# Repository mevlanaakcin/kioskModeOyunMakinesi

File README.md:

# kioskModeOyunMakinesi
Kiosk Modda çalışan eğlence amaçlı oyun makinesi<br>
<h3>PCB Tasarımı</h3><br>
Elektronik devre şeması ve PCB board tasarımı Eagle de tasarlandı.<br>

<h3>Yazılım</h3><br>
Yalım bölümü Atmega328-P işlemci kullanıldığından Raspberrypi ile tasarlanan kart arasında Serial haberleşme yapılmıştır. Kart üzerinde bulunan servo motorlar ile ödül dağıtım kanallarını kontrol edilmektedir. Görsel amaçlı kullanılan neopiksellerin yazılımsal kontrolleride yapılmıştır.

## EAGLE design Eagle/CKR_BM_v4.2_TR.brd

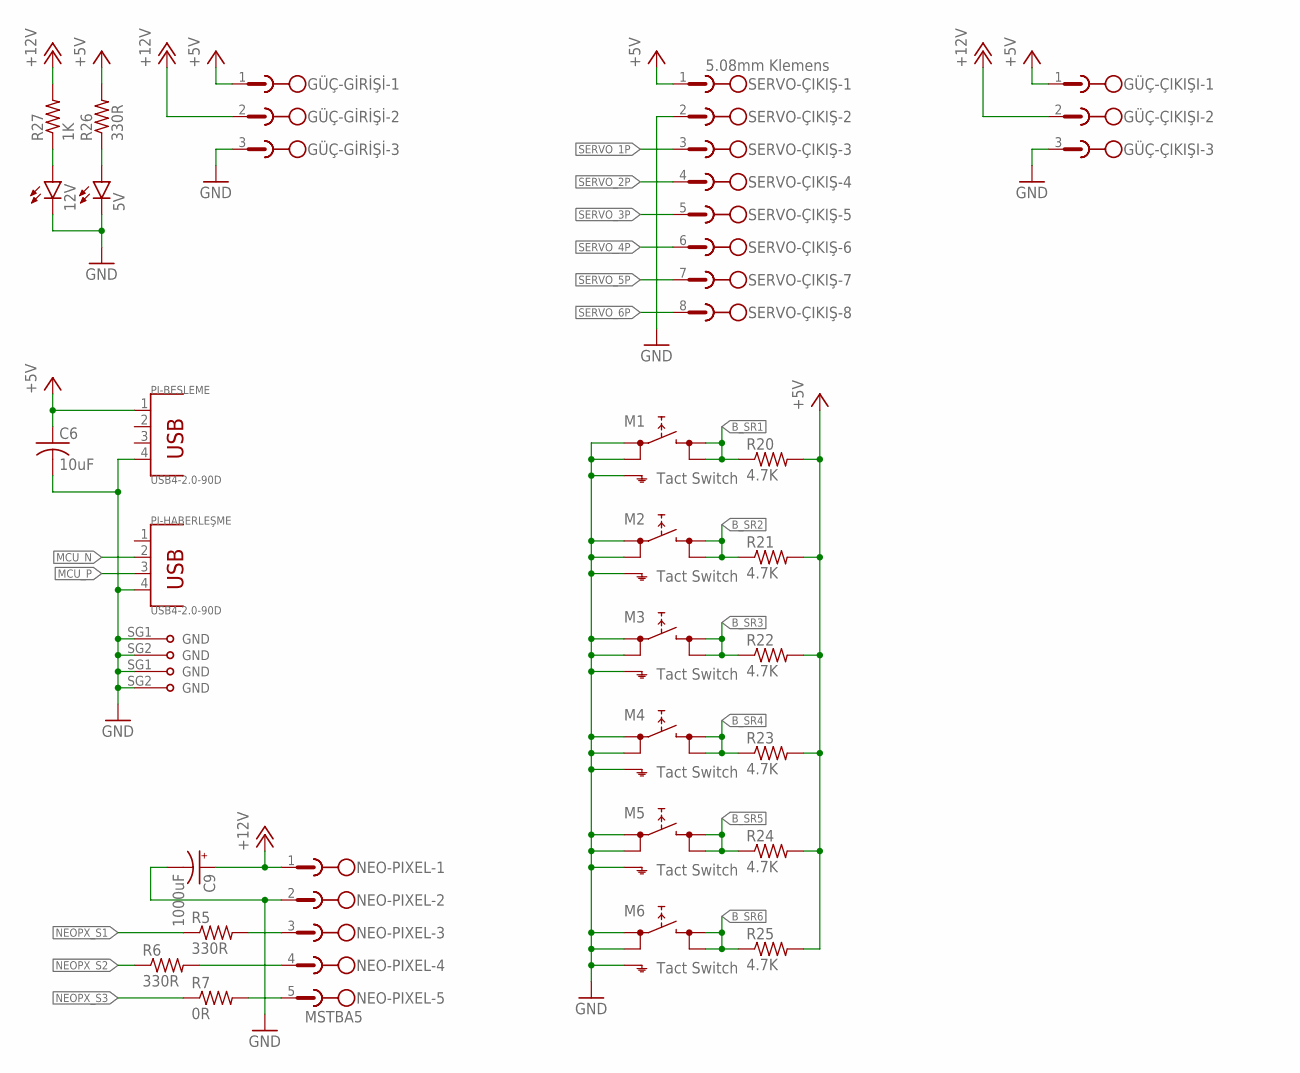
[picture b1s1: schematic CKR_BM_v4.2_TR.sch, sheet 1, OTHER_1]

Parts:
5V, 12V: LEDCHIP-LED0805; CHIP-LED0805
C6: 10uF; C0805
C9: 1000uF; 140CLH-1010
GÜÇ-GİRİŞİ: 5.08mm Klemens; MSTBA3
GÜÇ-ÇIKIŞI: 5.08mm Klemens; MSTBA3
M1, M2, M3, M4, M5, M6: Tact Switch; SKHMPXE010
NEO-PIXEL: MSTBA5
PI-BESLEME: USB4-2.0-90D; USB4+2P-2.0-90D
PI-HABERLEŞME: USB4-2.0-90D; USB4+2P-2.0-90D
R5, R6, R26: 330R; R0805
R7: 0R; R0805
R20, R21, R22, R23, R24, R25: 4.7K; R0805
R27: 1K; R0805
SERVO-ÇIKIŞ: 5.08mm Klemens; MSTBA8

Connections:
+5V: C6.1, GÜÇ-GİRİŞİ.1, GÜÇ-ÇIKIŞI.1, PI-BESLEME.1, R20.2, R21.2, R22.2, R23.2, R24.2, R25.2, R26.2, SERVO-ÇIKIŞ.1; also elsewhere on the board
+12V: C9.+, GÜÇ-GİRİŞİ.2, GÜÇ-ÇIKIŞI.2, NEO-PIXEL.1, R27.2; also elsewhere on the board
B_SR1: M1.3 (2.1), M1.4 (2.2), R20.1; also elsewhere on the board
B_SR2: M2.3 (2.1), M2.4 (2.2), R21.1; also elsewhere on the board
B_SR3: M3.3 (2.1), M3.4 (2.2), R22.1; also elsewhere on the board
B_SR4: M4.3 (2.1), M4.4 (2.2), R23.1; also elsewhere on the board
B_SR5: M5.3 (2.1), M5.4 (2.2), R24.1; also elsewhere on the board
B_SR6: M6.3 (2.1), M6.4 (2.2), R25.1; also elsewhere on the board
GND: 5V.C, 12V.C, C6.2, C9.-, GÜÇ-GİRİŞİ.3, GÜÇ-ÇIKIŞI.3, M1.1 (1.1), M1.2 (1.2), M1.5 (SH), M2.1 (1.1), M2.2 (1.2), M2.5 (SH), M3.1 (1.1), M3.2 (1.2), M3.5 (SH), M4.1 (1.1), M4.2 (1.2), M4.5 (SH), M5.1 (1.1), M5.2 (1.2), M5.5 (SH), M6.1 (1.1), M6.2 (1.2), M6.5 (SH), NEO-PIXEL.2, PI-BESLEME.4, PI-BESLEME.SG1 (GND), PI-BESLEME.SG2 (GND), PI-HABERLEŞME.4, PI-HABERLEŞME.SG1 (GND), PI-HABERLEŞME.SG2 (GND), SERVO-ÇIKIŞ.2; also elsewhere on the board
MCU_N: PI-HABERLEŞME.2; also elsewhere on the board
MCU_P: PI-HABERLEŞME.3; also elsewhere on the board
unnamed: NEO-PIXEL.3, R5.2
unnamed: NEO-PIXEL.4, R6.2
unnamed: NEO-PIXEL.5, R7.2
unnamed: 5V.A, R26.1
unnamed: 12V.A, R27.1
NEOPX_S1: R5.1; also elsewhere on the board
NEOPX_S2: R6.1; also elsewhere on the board
NEOPX_S3: R7.1; also elsewhere on the board
SERVO_1P: SERVO-ÇIKIŞ.3; also elsewhere on the board
SERVO_2P: SERVO-ÇIKIŞ.4; also elsewhere on the board
SERVO_3P: SERVO-ÇIKIŞ.5; also elsewhere on the board
SERVO_4P: SERVO-ÇIKIŞ.6; also elsewhere on the board
SERVO_5P: SERVO-ÇIKIŞ.7; also elsewhere on the board
SERVO_6P: SERVO-ÇIKIŞ.8; also elsewhere on the board

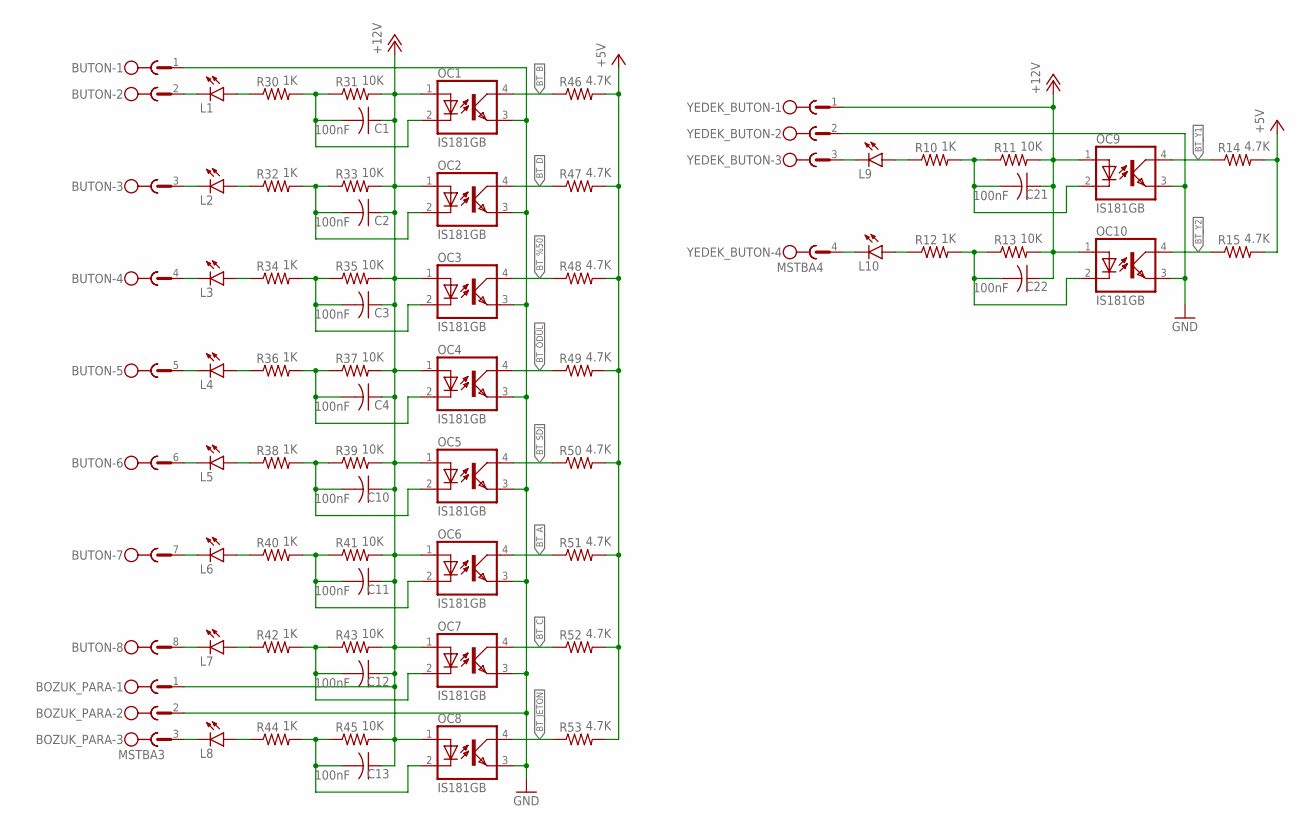
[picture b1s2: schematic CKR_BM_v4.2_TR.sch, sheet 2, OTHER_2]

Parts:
BOZUK_PARA: MSTBA3
BUTON: MSTBA8
C1, C2, C3, C4, C10, C11, C12, C13, C21, C22: 100nF; C0805
L1, L2, L3, L4, L5, L6, L7, L8, L9, L10: LEDCHIP-LED0805; CHIP-LED0805
OC1, OC2, OC3, OC4, OC5, OC6, OC7, OC8, OC9, OC10: IS181GB; SO-4
R10, R12, R30, R32, R34, R36, R38, R40, R42, R44: 1K; R0805
R11, R13, R31, R33, R35, R37, R39, R41, R43, R45: 10K; R0805
R14, R15, R46, R47, R48, R49, R50, R51, R52, R53: 4.7K; R0805
YEDEK_BUTON: MSTBA4

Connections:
+5V: R14.2, R15.2, R46.2, R47.2, R48.2, R49.2, R50.2, R51.2, R52.2, R53.2; also elsewhere on the board
+12V: BOZUK_PARA.1, C1.1, C2.1, C3.1, C4.1, C10.1, C11.1, C12.1, C13.1, C21.1, C22.1, OC1.1 (A), OC2.1 (A), OC3.1 (A), OC4.1 (A), OC5.1 (A), OC6.1 (A), OC7.1 (A), OC8.1 (A), OC9.1 (A), OC10.1 (A), R11.2, R13.2, R31.2, R33.2, R35.2, R37.2, R39.2, R41.2, R43.2, R45.2, YEDEK_BUTON.1; also elsewhere on the board
BT_%50: OC3.4 (COL), R48.1; also elsewhere on the board
BT_A: OC6.4 (COL), R51.1; also elsewhere on the board
BT_B: OC1.4 (COL), R46.1; also elsewhere on the board
BT_C: OC7.4 (COL), R52.1; also elsewhere on the board
BT_D: OC2.4 (COL), R47.1; also elsewhere on the board
BT_JETON: OC8.4 (COL), R53.1; also elsewhere on the board
BT_SDJ: OC5.4 (COL), R50.1; also elsewhere on the board
BT_Y1: OC9.4 (COL), R14.1; also elsewhere on the board
BT_Y2: OC10.4 (COL), R15.1; also elsewhere on the board
BT_ÖDÜL: OC4.4 (COL), R49.1; also elsewhere on the board
GND: BOZUK_PARA.2, BUTON.1, OC1.3 (EMIT), OC2.3 (EMIT), OC3.3 (EMIT), OC4.3 (EMIT), OC5.3 (EMIT), OC6.3 (EMIT), OC7.3 (EMIT), OC8.3 (EMIT), OC9.3 (EMIT), OC10.3 (EMIT), YEDEK_BUTON.2; also elsewhere on the board
unnamed: L1.A, R30.1
unnamed: C1.2, OC1.2 (C), R30.2, R31.1
unnamed: L9.A, R10.1
unnamed: BUTON.2, L1.C
unnamed: BOZUK_PARA.3, L8.C
unnamed: L2.A, R32.1
unnamed: C2.2, OC2.2 (C), R32.2, R33.1
unnamed: C21.2, OC9.2 (C), R10.2, R11.1
unnamed: BUTON.8, L7.C
unnamed: L3.A, R34.1
unnamed: C3.2, OC3.2 (C), R34.2, R35.1
unnamed: L9.C, YEDEK_BUTON.3
unnamed: BUTON.7, L6.C
unnamed: L4.A, R36.1
unnamed: C4.2, OC4.2 (C), R36.2, R37.1
unnamed: L10.A, R12.1
unnamed: BUTON.6, L5.C
unnamed: L5.A, R38.1
unnamed: C10.2, OC5.2 (C), R38.2, R39.1
unnamed: C22.2, OC10.2 (C), R12.2, R13.1
unnamed: BUTON.5, L4.C
unnamed: L6.A, R40.1
unnamed: C11.2, OC6.2 (C), R40.2, R41.1
unnamed: L10.C, YEDEK_BUTON.4
unnamed: BUTON.4, L3.C
unnamed: L7.A, R42.1
unnamed: C12.2, OC7.2 (C), R42.2, R43.1
unnamed: BUTON.3, L2.C
unnamed: L8.A, R44.1
unnamed: C13.2, OC8.2 (C), R44.2, R45.1

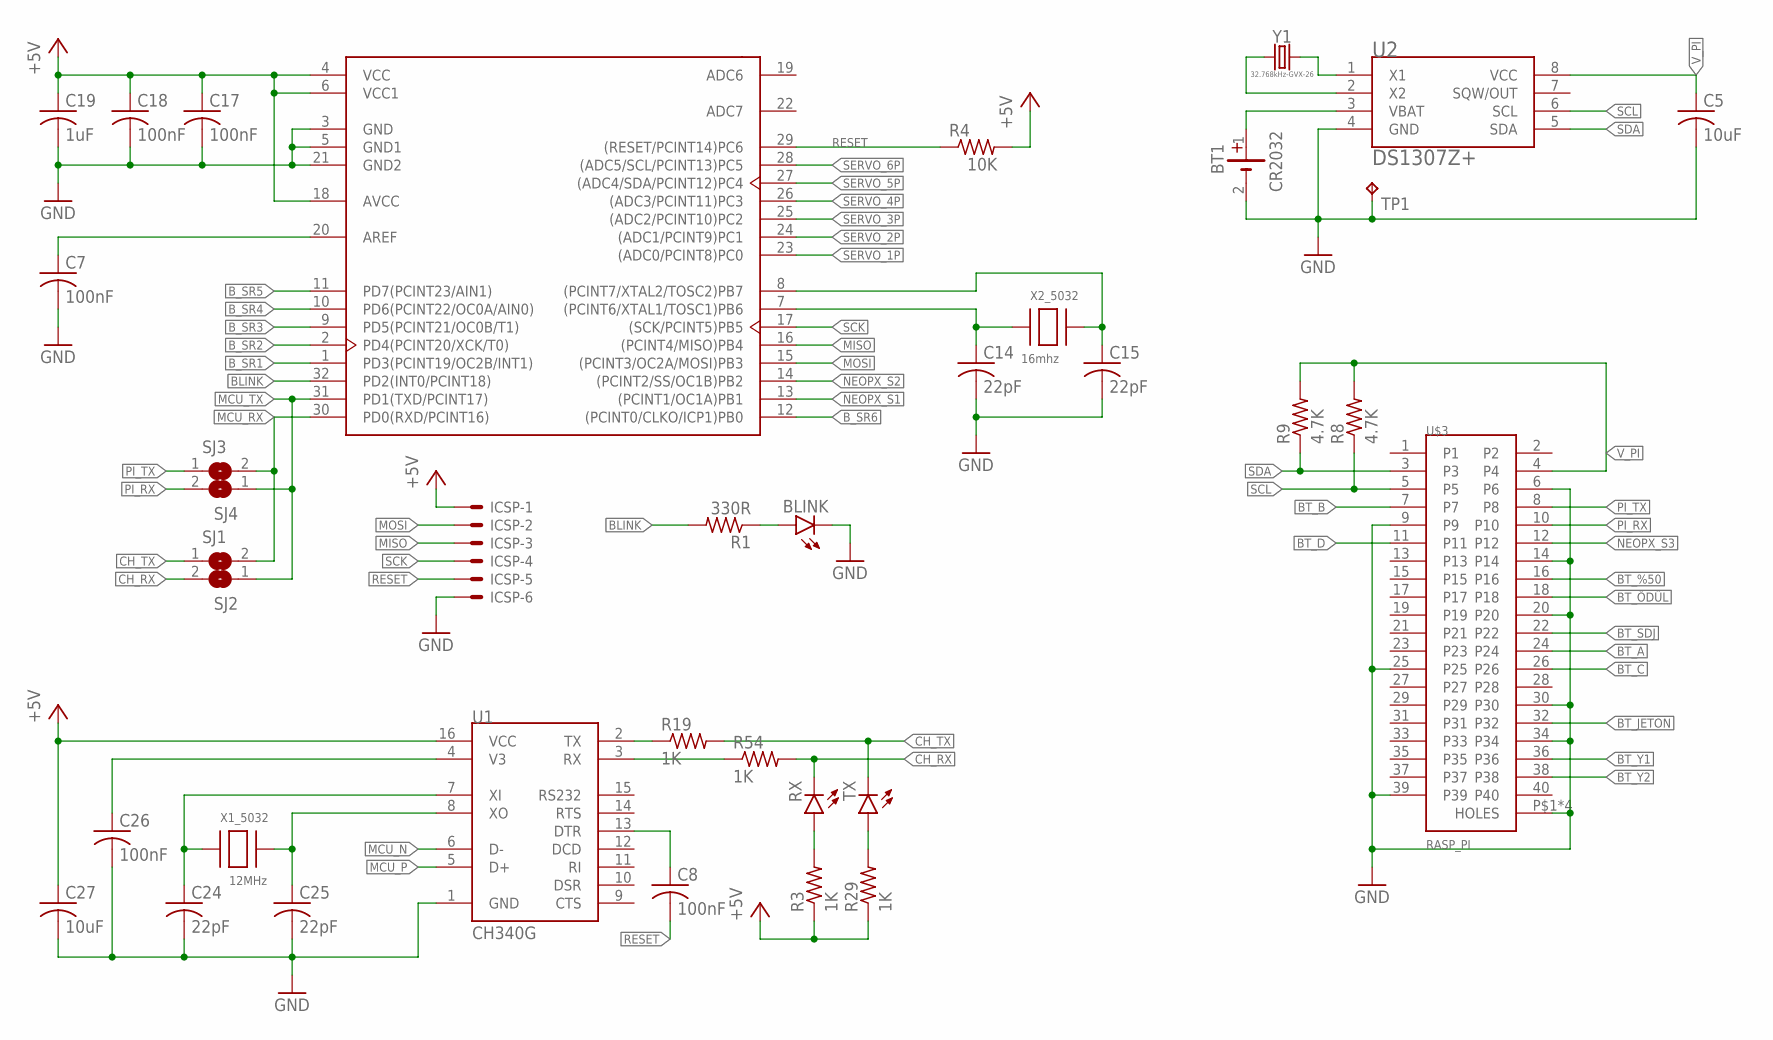
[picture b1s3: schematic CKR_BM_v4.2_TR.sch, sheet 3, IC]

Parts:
BLINK: LEDCHIP-LED0805; CHIP-LED0805
BT1: CR2032; 79528211
C5, C27: 10uF; C0805
C7, C8, C17, C18, C26: 100nF; C0805
C14, C15, C24, C25: 22pF; C0805
C19: 1uF; C0805
ICSP: C-GRID-06-70543; 70543-06
R1: 330R; R0805
R3, R19, R29, R54: 1K; R0805
R4: 10K; R0805
R8, R9: 4.7K; R0805
RX: LEDCHIP-LED0805; CHIP-LED0805
SJ1, SJ2, SJ3, SJ4: SJ
TP1: GND; TP15R
TX: LEDCHIP-LED0805; CHIP-LED0805
U1: CH340G; SOIC16
U2: DS1307Z+; SOIC-8N
U4: ATMEGA328P-AU; TQFP-32
U$3: RASP_PI
X1_5032: 12MHz; NX5032
X2_5032: 16mhz; NX5032
Y1: 32.768kHz-GVX-26; CRYSTAL-PTH-2X6-CYL

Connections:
+5V: C17.1, C18.1, C19.1, C27.1, ICSP.1, R3.1, R4.2, R29.1, U1.16 (VCC), U4.4 (VCC), U4.6 (VCC1), U4.18 (AVCC); also elsewhere on the board
BLINK: R1.2, U4.32 (PD2(INT0/PCINT18))
BT_%50: U$3.16; also elsewhere on the board
BT_A: U$3.24; also elsewhere on the board
BT_B: U$3.7; also elsewhere on the board
BT_C: U$3.26; also elsewhere on the board
BT_D: U$3.11; also elsewhere on the board
BT_JETON: U$3.32; also elsewhere on the board
BT_SDJ: U$3.22; also elsewhere on the board
BT_Y1: U$3.36; also elsewhere on the board
BT_Y2: U$3.38; also elsewhere on the board
BT_ÖDÜL: U$3.18; also elsewhere on the board
B_SR1: U4.1 (PD3(PCINT19/OC2B/INT1)); also elsewhere on the board
B_SR2: U4.2 (PD4(PCINT20/XCK/T0)); also elsewhere on the board
B_SR3: U4.9 (PD5(PCINT21/OC0B/T1)); also elsewhere on the board
B_SR4: U4.10 (PD6(PCINT22/OC0A/AIN0)); also elsewhere on the board
B_SR5: U4.11 (PD7(PCINT23/AIN1)); also elsewhere on the board
B_SR6: U4.12 ((PCINT0/CLKO/ICP1)PB0); also elsewhere on the board
CH_RX: R54.2, RX.C, SJ2.2
CH_TX: R19.2, SJ1.1, TX.C
GND: BLINK.C, BT1.2 (-), C5.2, C7.2, C14.2, C15.2, C17.2, C18.2, C19.2, C24.2, C25.2, C26.2, C27.2, ICSP.6, TP1.TP, U1.1 (GND), U2.4 (GND), U4.3 (GND), U4.5 (GND1), U4.21 (GND2), U$3.6, U$3.9, U$3.14, U$3.20, U$3.25, U$3.30, U$3.34, U$3.39, U$3.P$1 (HOLES), U$3.P$2 (HOLES), U$3.P$3 (HOLES), U$3.P$4 (HOLES); also elsewhere on the board
MCU_N: U1.6 (D-); also elsewhere on the board
MCU_P: U1.5 (D+); also elsewhere on the board
MCU_RX: SJ1.2, SJ3.2, U4.30 (PD0(RXD/PCINT16))
MCU_TX: SJ2.1, SJ4.1, U4.31 (PD1(TXD/PCINT17))
MISO: ICSP.3, U4.16 ((PCINT4/MISO)PB4)
MOSI: ICSP.2, U4.15 ((PCINT3/OC2A/MOSI)PB3)
unnamed: BT1.1 (+), U2.3 (VBAT)
unnamed: U2.2 (X2), Y1.1
unnamed: U2.1 (X1), Y1.2
unnamed: R3.2, RX.A
unnamed: R29.2, TX.A
unnamed: C14.1, U4.7 ((PCINT6/XTAL1/TOSC1)PB6), X2_5032.P$1
unnamed: C8.1, U1.13 (DTR)
unnamed: C26.1, U1.4 (V3)
unnamed: C24.1, U1.7 (XI), X1_5032.P$1
unnamed: C25.1, U1.8 (XO), X1_5032.P$2
unnamed: R19.1, U1.2 (TX)
unnamed: R54.1, U1.3 (RX)
unnamed: BLINK.A, R1.1
unnamed: C7.1, U4.20 (AREF)
unnamed: C15.1, U4.8 ((PCINT7/XTAL2/TOSC2)PB7), X2_5032.P$2
NEOPX_S1: U4.13 ((PCINT1/OC1A)PB1); also elsewhere on the board
NEOPX_S2: U4.14 ((PCINT2/SS/OC1B)PB2); also elsewhere on the board
NEOPX_S3: U$3.12; also elsewhere on the board
PI_RX: SJ4.2, U$3.10
PI_TX: SJ3.1, U$3.8
RESET: C8.2, ICSP.5, R4.1, U4.29 ((RESET/PCINT14)PC6)
SCK: ICSP.4, U4.17 ((SCK/PCINT5)PB5)
SCL: R8.1, U2.6 (SCL), U$3.5
SDA: R9.1, U2.5 (SDA), U$3.3
SERVO_1P: U4.23 ((ADC0/PCINT8)PC0); also elsewhere on the board
SERVO_2P: U4.24 ((ADC1/PCINT9)PC1); also elsewhere on the board
SERVO_3P: U4.25 ((ADC2/PCINT10)PC2); also elsewhere on the board
SERVO_4P: U4.26 ((ADC3/PCINT11)PC3); also elsewhere on the board
SERVO_5P: U4.27 ((ADC4/SDA/PCINT12)PC4); also elsewhere on the board
SERVO_6P: U4.28 ((ADC5/SCL/PCINT13)PC5); also elsewhere on the board
V_PI: C5.1, R8.2, R9.2, U2.8 (VCC), U$3.4

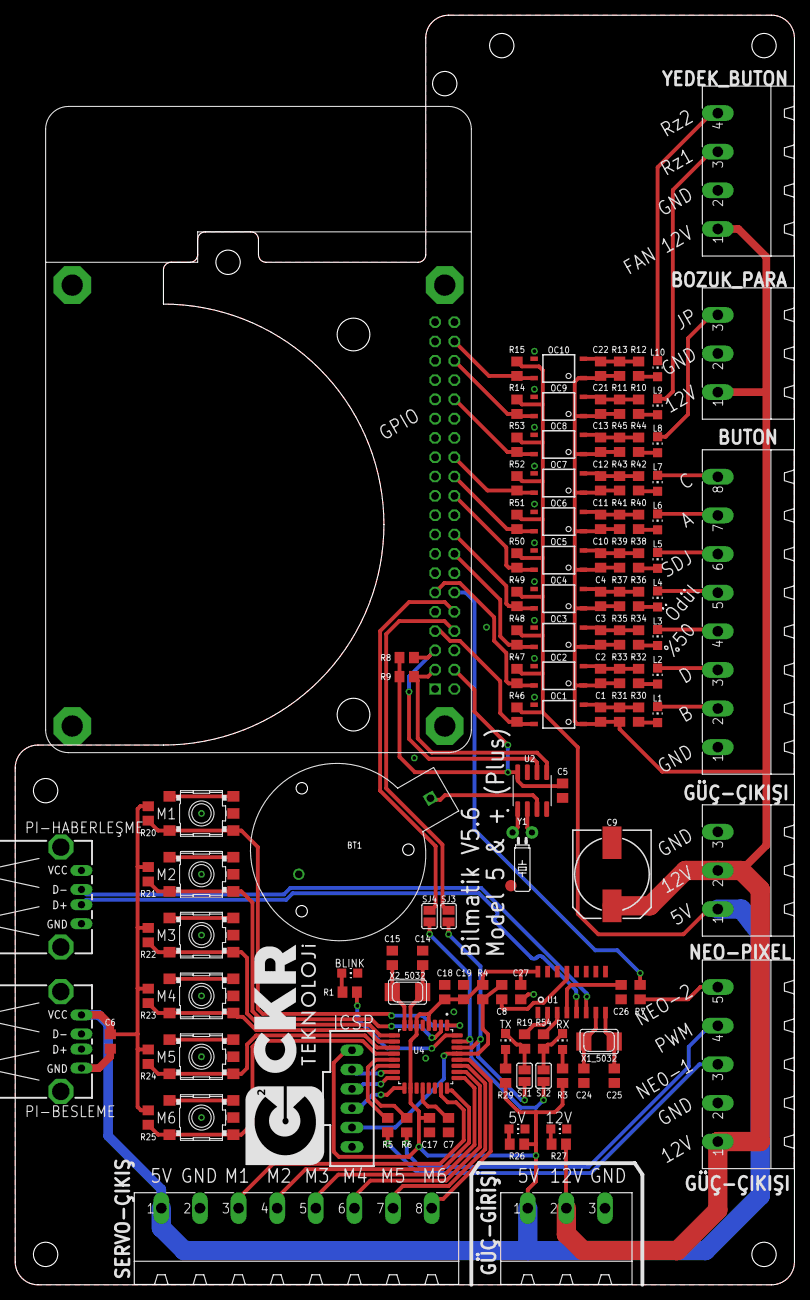
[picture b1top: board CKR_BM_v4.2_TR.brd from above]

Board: 2 copper layers, 102.5 x 167.0 mm, 127 parts (1 on the bottom side), 94 nets.

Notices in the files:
parts and their libraries:
SparkFun-Clocks: Licensing: Creative Commons ShareAlike 4.0 International - https://creativecommons.org/licenses/by-sa/4.0
